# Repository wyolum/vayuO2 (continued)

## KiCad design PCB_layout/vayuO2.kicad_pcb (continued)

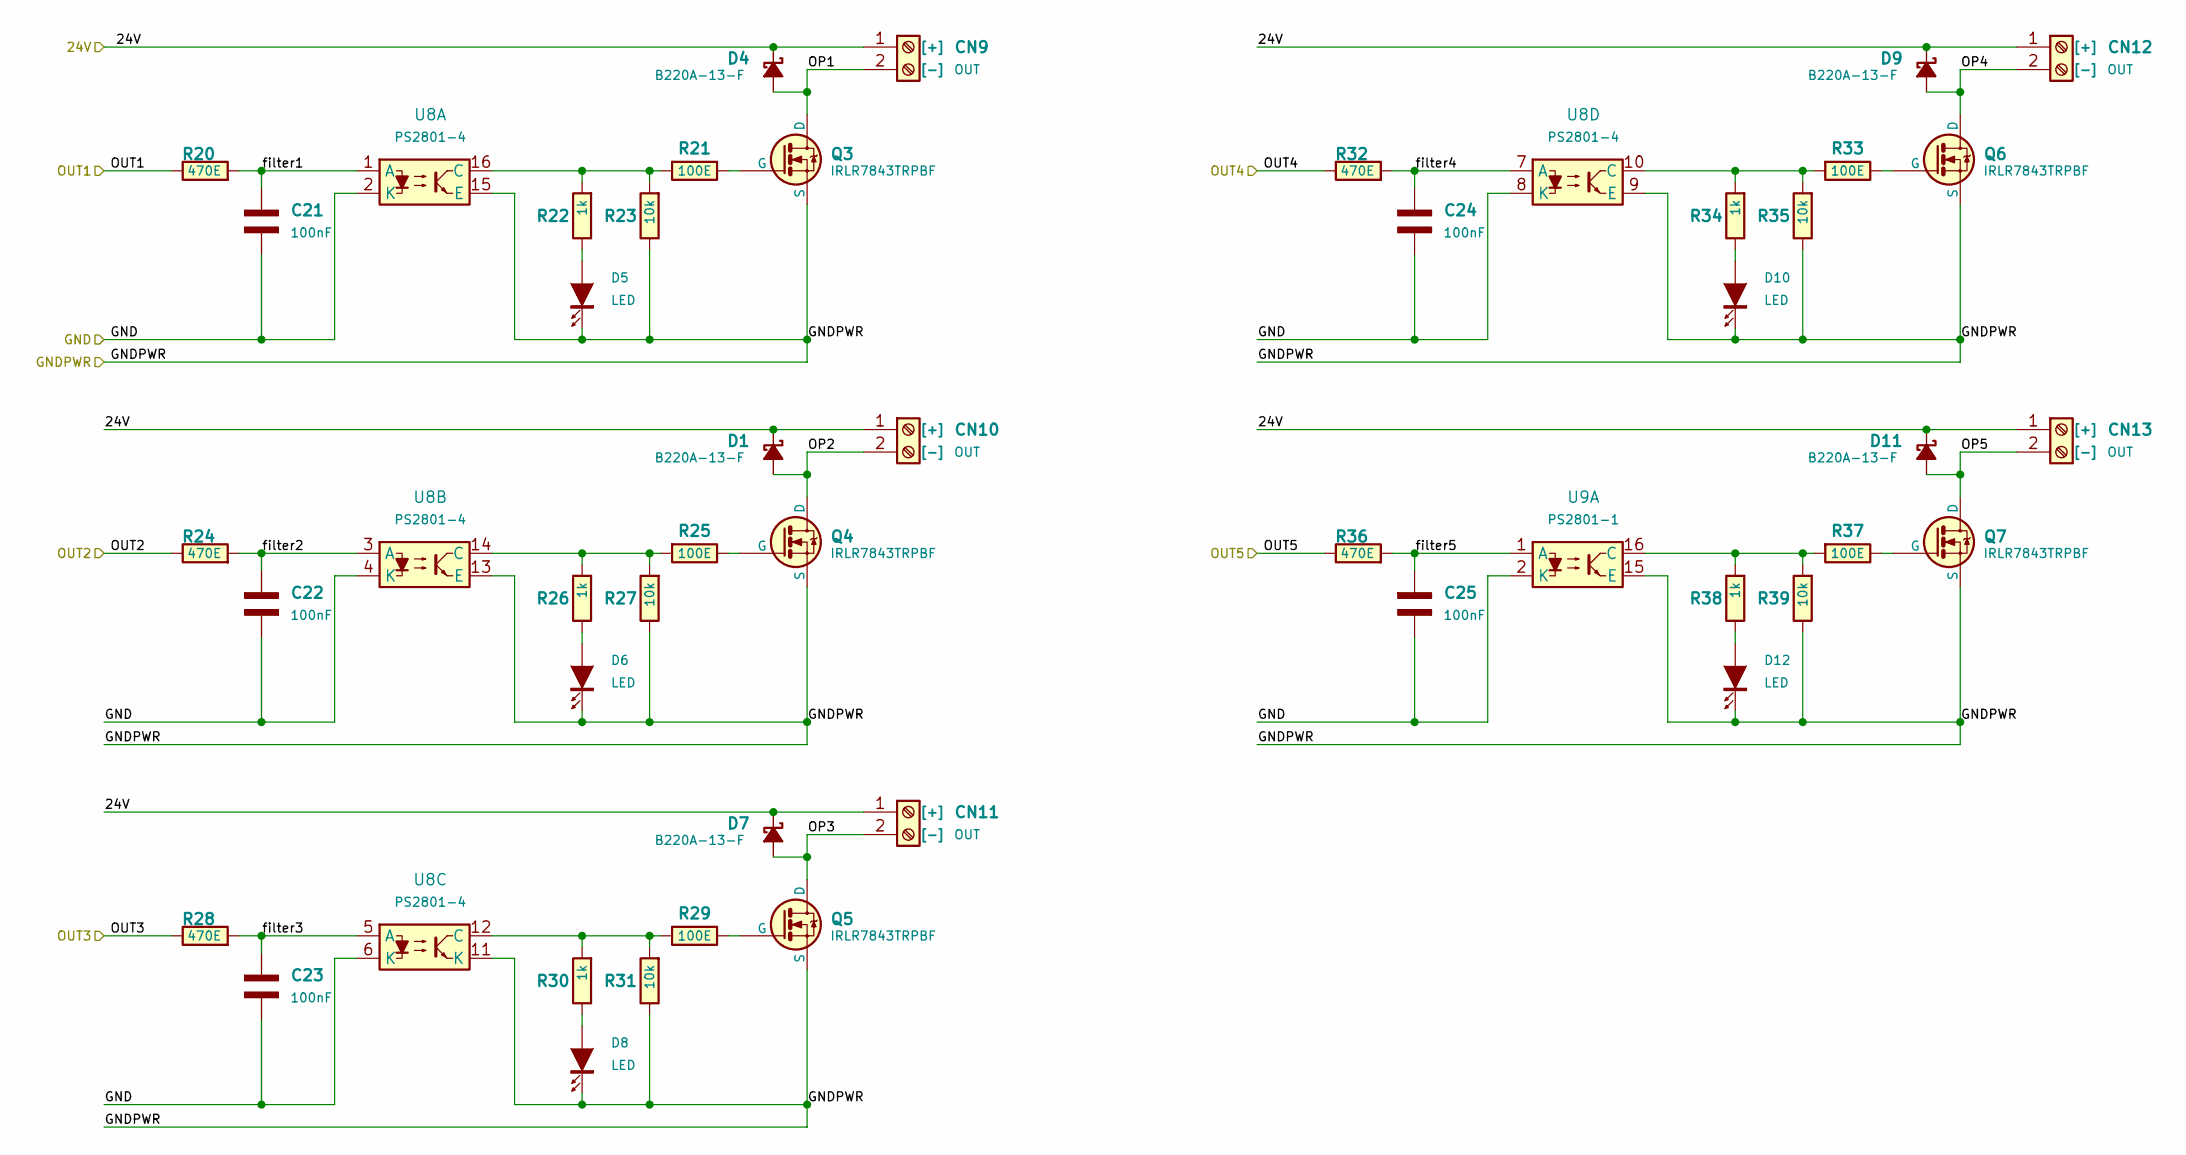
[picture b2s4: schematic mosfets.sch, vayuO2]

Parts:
C21, C22, C23, C24, C25: 100nF; C_0603_1608Metric
CN9, CN10, CN11, CN12, CN13: OUT; TerminalBlock_Wurth_1377-2_Horizontal
D1, D4, D7, D9, D11: B220A-13-F; D_SMB
D5, D6, D8, D10, D12: LED; LED_0603_1608Metric
Q3, Q4, Q5, Q6, Q7: IRLR7843TRPBF; MOSFET_D_PAK
R20, R24, R28, R32, R36: 470E; R_0603_1608Metric
R21, R25, R29, R33, R37: 100E; R_0603_1608Metric
R22, R26, R30, R34, R38: 1k; R_0603_1608Metric
R23, R27, R31, R35, R39: 10k; R_0603_1608Metric
U8: PS2801-4; SO-16_5.3x10.2mm_P1.27mm
U9: PS2801-1; SO-4_5.3x2.7mm_P1.27mm

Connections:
+24V: CN9.1, CN10.1, CN11.1, CN12.1, CN13.1, D1.1 (K), D4.1 (K), D7.1 (K), D9.1 (K), D11.1 (K); also elsewhere on the board
/OUT1: R20.1; also elsewhere on the board
/OUT2: R24.1; also elsewhere on the board
/OUT3: R28.1; also elsewhere on the board
/OUT4: R32.1; also elsewhere on the board
/OUT5: R36.1; also elsewhere on the board
/mosfets/OP1: CN9.2, D4.2 (A), Q3.2 (D)
/mosfets/OP2: CN10.2, D1.2 (A), Q4.2 (D)
/mosfets/OP3: CN11.2, D7.2 (A), Q5.2 (D)
/mosfets/OP4: CN12.2, D9.2 (A), Q6.2 (D)
/mosfets/OP5: CN13.2, D11.2 (A), Q7.2 (D)
/mosfets/filter1: C21.1 (+), R20.2, U8.1 (A)
/mosfets/filter2: C22.1 (+), R24.2, U8.3 (A)
/mosfets/filter3: C23.1 (+), R28.2, U8.5 (A)
/mosfets/filter4: C24.1 (+), R32.2, U8.7 (A)
/mosfets/filter5: C25.1 (+), R36.2, U9.1 (A)
GNDPWR: D5.2 (K), D6.2 (K), D8.2 (K), D10.2 (K), D12.2 (K), Q3.3 (S), Q4.3 (S), Q5.3 (S), Q6.3 (S), Q7.3 (S), R23.1, R27.1, R31.1, R35.1, R39.1, U8.9 (E), U8.11 (K), U8.13 (E), U8.15 (E), U9.15 (E); also elsewhere on the board
unnamed: D5.1 (A), R22.1
unnamed: D6.1 (A), R26.1
unnamed: D8.1 (A), R30.1
unnamed: D10.1 (A), R34.1
unnamed: D12.1 (A), R38.1
unnamed: Q3.1 (G), R21.1
unnamed: Q4.1 (G), R25.1
unnamed: Q5.1 (G), R29.1
unnamed: Q6.1 (G), R33.1
unnamed: Q7.1 (G), R37.1
unnamed: R21.2, R22.2, R23.2, U8.16 (C)
unnamed: R25.2, R26.2, R27.2, U8.14 (C)
unnamed: R29.2, R30.2, R31.2, U8.12 (C)
unnamed: R33.2, R34.2, R35.2, U8.10 (C)
unnamed: R37.2, R38.2, R39.2, U9.16 (C)

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
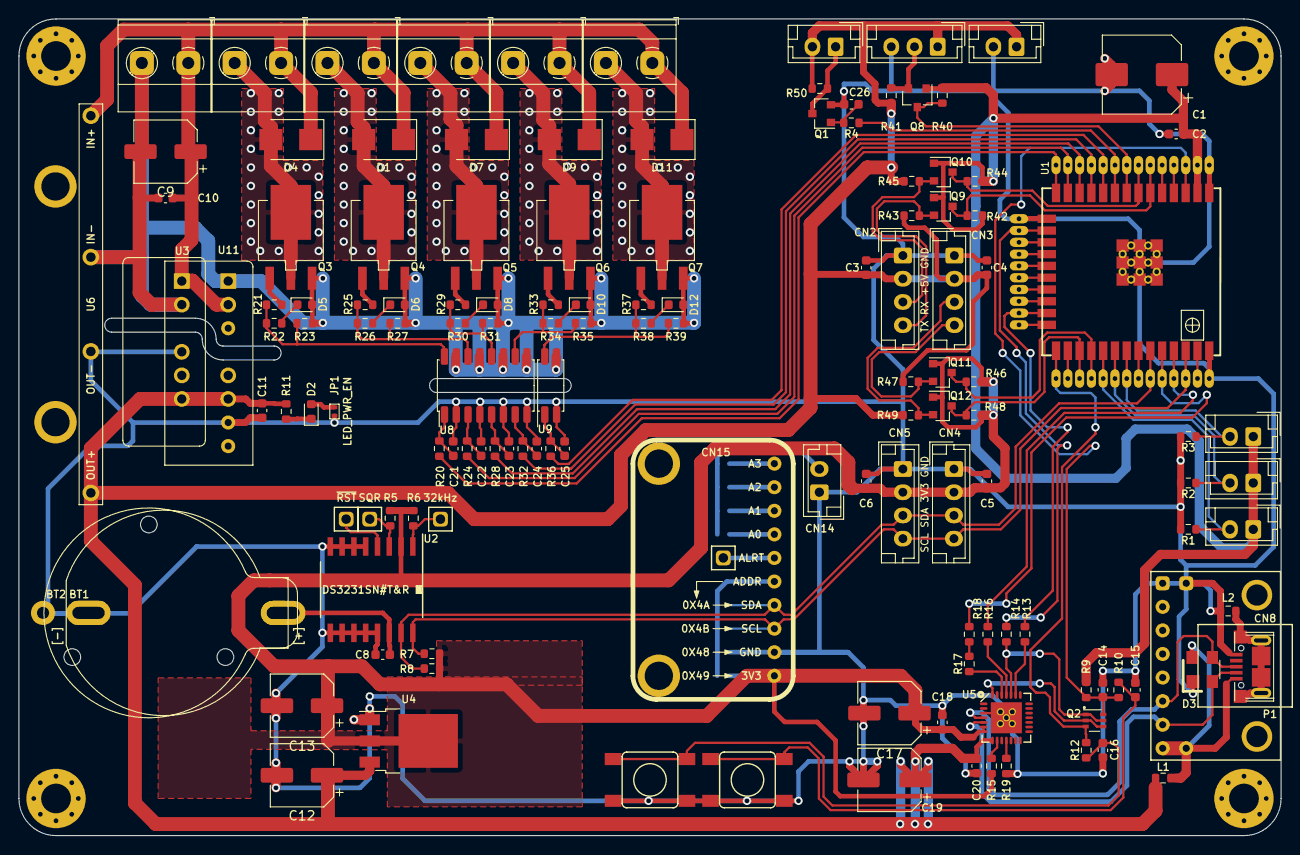
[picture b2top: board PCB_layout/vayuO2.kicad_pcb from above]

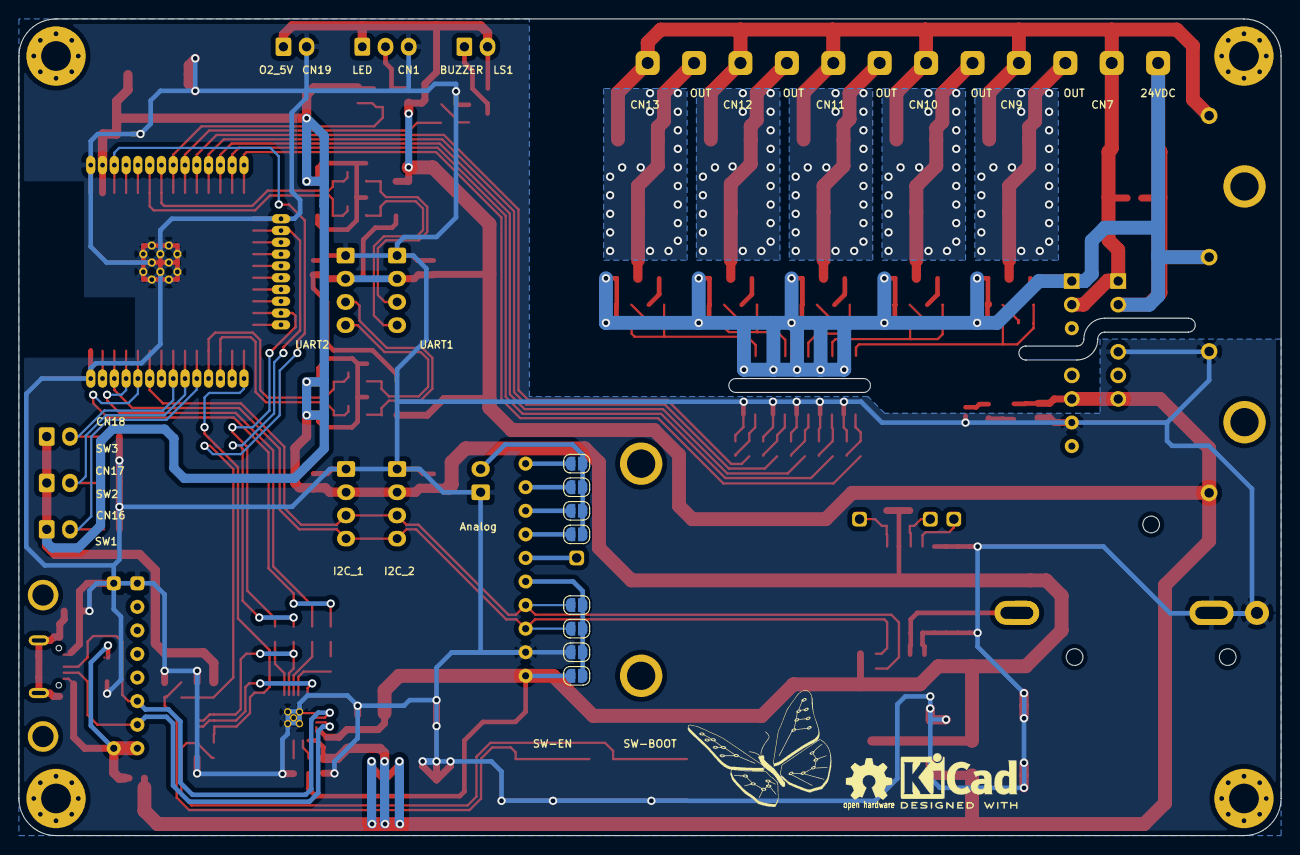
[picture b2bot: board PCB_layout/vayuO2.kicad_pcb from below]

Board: 2 copper layers, 136.0 x 88.0 mm, 154 parts (11 on the bottom side), 86 nets.

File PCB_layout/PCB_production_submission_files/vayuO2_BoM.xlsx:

Id | Designator | Package | Quantity | Designation | Supplier and ref | MFR P/N & LCSC Link
1 | C1 | CP_Elec_10x10 | 1 | 100uF/6V3 | C176665 | VEJ101M1HTR-0810L
2 | C2 | C_0603_1608Metric | 1 | 1uF/10V | C29936 | CL10B105KA8NNNC
3 | C12,C19,C17,C9 | CP_Elec_6.3x7.7 | 4 | 10uF/25V | C134747 | VEJ100M2ATR-0607
4 | C13 | CP_Elec_6.3x7.7 | 1 | 22uF/25V | C134761 | VEJ220M1JTR-0607
5 | C16,C15,C14 | C_0603_1608Metric | 3 | 1nF | C153291 | CL10B102KC8NNNC
6 | C25,C26,C24,C23,C22,C21,C20,C18,C11,C10,C8,C6,C5,C4,C3 | C_0603_1608Metric | 15 | 100nF | C24452 | CL10B104JB8NNNC
7 | CN8 | USB_Micro-B_seeed-320010561 | 1 | USB_micro | NO SOURCE FOUND
8 | D2 | LED_0603_1608Metric | 1 | LED_PWR | C72044 | 19-217/R6C-AL1M2VY/3T
9 | D3 | SOT-143 | 1 | PRTR5V0U2X | C316030 | PRTR5V0U2X-N
10 | D11,D9,D7,D4,D1 | D_SMB | 5 | B220A-13-F | C110481 | B220A-13-F
11 | D12,D10,D8,D6,D5 | LED_0603_1608Metric | 5 | LED | C72044 | 19-217/R6C-AL1M2VY/3T
12 | L2,L1 | R_0603_1608Metric | 2 | 330E | C1002 | GZ1608D601TF
13 | Q1 | SOT-23 | 1 | MMBT3904 | C84104 | MMBT3904
14 | Q2 | SOT-363_SC-70-6 | 1 | DTC123YCA | C56452 | DTC123YCA
15 | Q5,Q3,Q7,Q6,Q4 | MOSFET_D_PAK | 5 | IRLR7843TRPBF | C21988 | IRLR7843TRPBF
16 | Q12,Q11,Q10,Q9,Q8 | SOT-23 | 5 | BSS138 | C24553 | BSS138W-7-F
17 | R4 | R_0603_1608Metric | 1 | 220E | C269445 | RMC06032201%N
18 | R8,R7 | R_0603_1608Metric | 2 | 4K7 | C105428 | RC0603JR-074K7L
19 | R11,R30,R50,R38,R34,R26,R22,R15 | R_0603_1608Metric | 8 | 1k | C14676 | RC0603JR-071KL
20 | R13,R14 | R_0603_1608Metric | 2 | 0E NC | -- | --
21 | R18,R16 | R_0603_1608Metric | 2 | 0E | -- | --
22 | R27,R19,R49,R48,R47,R46,R45,R44,R43,R42,R41,R40,R39,R35,R31,R23,R9,R6,R5,R3,R2,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 | R_0603_1608Metric | 22 | 10k | C25804 | 0603WAF1002T5E
23 | R36,R32,R28,R24,R20,R17,R12,R10 | R_0603_1608Metric | 8 | 470E | C176130 | QR0603F470RP05Z
24 | R37,R33,R29,R25,R21 | R_0603_1608Metric | 5 | 100E | C176153 | QR0603J10R0P05Z
25 | S4 | SW_SMD_311020004 | 1 | SW-EN | -- | DTSM-61R-V-T/R
26 | S5 | SW_SMD_311020004 | 1 | SW-BOOT | -- | DTSM-61R-V-T/R
27 | U1 | ESP_wroom_32 | 1 | ESP32-WROOM-32UC | C328062 | ESP32-WROOM-32U | MOQ 650
28 | U2 | DS3231 | 1 | DS3231N | C9866 | DS3231SN#T&R | MOQ 1000
29 | U4 | TO-252-3_TabPin2 | 1 | LM1117-33 | C165080 | BL1117-33CY
30 | U5 | QFN-28-1EP_5x5mm_Pitch0.5mm | 1 | CP2102N-A01-GQFN28 | C105167 | CP2102N-A01-GQFN28R | MOQ 1500
31 | U8 | SO-16_5.3x10.2mm_P1.27mm | 1 | PS2801-4 | C89880 | PS2801-4 | No Stock
32 | U9 | SO-4_5.3x2.7mm_P1.27mm | 1 | PS2801-1 | C133880 | PS2801-1-F3
33 | BT1 | cr2032_02 | 1 | Batt_RTC
34 | BT2 | cr2032_03 | 1 | Batt_RTC
35 | CN1 | JST_EH_B3B-EH-A_1x03_P2.50mm_Vertical | 1 | Conn_LED
36 | CN2 | JST_EH_B4B-EH-A_1x04_P2.50mm_Vertical | 1 | UART1
37 | CN3 | JST_EH_B4B-EH-A_1x04_P2.50mm_Vertical | 1 | UART2
38 | CN4 | JST_EH_B4B-EH-A_1x04_P2.50mm_Vertical | 1 | I2C_1
39 | CN5 | JST_EH_B4B-EH-A_1x04_P2.50mm_Vertical | 1 | I2C_2
40 | CN7 | TerminalBlock_Wurth_1377-2_Horizontal | 1 | 24VDC
41 | CN13,CN12,CN11,CN10,CN9 | TerminalBlock_Wurth_1377-2_Horizontal | 5 | OUT
42 | CN14 | JST_EH_B2B-EH-A_1x02_P2.50mm_Vertical | 1 | Conn_Analog
43 | CN15 | ADS1115 | 1 | Conn_ADS1115
44 | CN16 | JST_EH_B2B-EH-A_1x02_P2.50mm_Vertical | 1 | Conn_S1
45 | CN17 | JST_EH_B2B-EH-A_1x02_P2.50mm_Vertical | 1 | Conn_S2
46 | CN18 | JST_EH_B2B-EH-A_1x02_P2.50mm_Vertical | 1 | Conn_S3
47 | CN19 | JST_EH_B2B-EH-A_1x02_P2.50mm_Vertical | 1 | Conn_O2_5V
48 | LS1 | JST_EH_B2B-EH-A_1x02_P2.50mm_Vertical | 1 | Piezo
49 | P1 | USB-C_bout | 1 | USB-C_breakout
50 | U3 | DC_DC_conv_2W | 1 | B2405S-2WR2
51 | U6 | DC_DC_buck_LM2596_Vertical | 1 | 24V_BUCK
52 | U11 | DC_DC_conv_6W | 1 | DC_DC_buck_6W

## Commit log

2021-10-02 first commit, vayuO2 oxygen concentrator controller
2021-10-03 added optocoupler for isolation
2021-10-04 PCB layout, WIP
2021-10-06 BOM, WIP
2021-10-07 final production files generated
2021-10-07 fixed rotations in position CPL file
2021-10-10 version 2 ready - using ESP32 DOIT dev board module
2021-10-11 version 2 ready - production files generated
2021-10-13 ver 3 with TO-263 D2PAK Mosfets
2021-10-14 Updated component footprint
    * Updated opto IC footprint
2021-10-14 ver 3 production files ready
2021-11-30 ver 4 with revised MOSFET output
